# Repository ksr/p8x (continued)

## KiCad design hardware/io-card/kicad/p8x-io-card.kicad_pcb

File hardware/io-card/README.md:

# I/O Card

> **Theory of operation:** [p8x-io-card-theory.md](p8x-io-card-theory.md) — deep walkthrough of inputs/outputs, signal flow, and logic.

All memory-mapped I/O lives here: an 8-switch input port, an 8-LED output port,
**two** RS-232 serial channels via 6850 ACIAs (rev B), and a passive **bus-monitor**
LED display that turns the machine into an Altair-style "watch it think" front panel.

> **Rev B (2026-09-19)** — the routed KiCad board in [`kicad/`](kicad/README.md)
> (not yet fabricated) adds a second 6850 (**U17**, ACIA2 at `$FF08/09`, the
> Kermit / serial-terminal port) on the MAX232's second channel, with its E-gate
> inverter in **U18** (74HCT14). Each channel has its own **DB9** socket and a
> 2×3 jumper block that swaps RX/TX (straight or null-modem). A DS1302 real-time
> clock (**U16**) is provisioned but not fitted (DNP): it is a bit-banged 3-wire
> part on header J3, not memory-mapped. The text below describes the rev A
> circuit, which rev B keeps.

| Address | Port |
|---------|------|
| `$FF00` | Switch input — 8 toggle switches → data bus on read |
| `$FF02` | LED output — 74374 latch → 8 LEDs on write |
| `$FF04` | 6850 ACIA control/status |
| `$FF05` | 6850 ACIA data (RS-232 TX/RX) |
| `$FF08` | ACIA2 control/status (rev B) |
| `$FF09` | ACIA2 data (rev B) |

> This README describes the circuit as actually built in
> [`generators/gen_eagle.py`](../../generators/gen_eagle.py). See
> [p8x-system-design.md §7](../../docs/p8x-system-design.md) for the overview and
> [p8x-bus-definition.md](../backplane/p8x-bus-definition.md) for bus pins.

## Chip inventory

| Ref | Device | Role |
|-----|--------|------|
| U1 | 7430 | 8-input NAND — I/O page ($FFxx) detector |
| U2 | 74138 | Port decoder (A1–A3 → up to 8 port selects) |
| U3 | 74138 | DOE decoder (read enable) |
| U4 | 74138 | DLD decoder (write strobe) |
| U5 | 74HCT32 | OR glue (read/write strobe gating) |
| U6 | 74HCT08 | AND glue (ACIA enable) |
| U7 | 74161 | Baud-rate divider |
| U8 | MAX232 | RS-232 level shifter (the one non-TTL part) |
| U9 | 74244 | Switch-input buffer |
| U10 | 74374 | LED output latch |
| U11–U13 | 74244 | Bus monitors — A0–7, A8–15, D0–7 |
| U14 | 6850 | ACIA (asynchronous serial) |
| U15 | 74HCT00 | NAND glue |
| U16 | DS1302 | Real-time clock, DNP (rev B; 3-wire on J3, not memory-mapped) |
| U17 | 6850 | ACIA2 at `$FF08/09` (rev B) |
| U18 | 74HCT14 | Inverter — ACIA2 enable gate (rev B) |
| X2 | 2.4576 MHz osc | Baud clock source |

## How it works

### Port decoding
U1 (7430) detects the `$FFxx` page exactly as on the memory card. Within the page,
U2 (74138) decodes the low address lines into individual port selects (`-P0`, `-P1`,
`-P2`, …). Read vs write comes from the DOE decoder (U3 → `-RD`) and DLD decoder
(U4 → `-MEMW`), gated in U5/U6 into per-port read/write strobes.

### Switch input ($FF00)
Eight toggle switches with a SIP pull-up network feed a 74244 (U9). On a read of
`$FF00`, U9 is enabled and drives the switch states onto D0–D7.

### LED output ($FF02)
On a write to `$FF02`, the 74374 (U10) latches D0–D7. Its outputs drive an LED bank
through series-resistor networks, so the port value is visible at a glance.

### Serial (6850 ACIA, $FF04–$FF05)
The **6850 ACIA** (U14) handles asynchronous serial. Its enable is the `$FF04/05`
port select gated with the clock (U6/U15) for correct E-clock timing. A **74161**
(U7) divides the dedicated **2.4576 MHz** oscillator (X2) by 16 to make the
TX/RX baud clock. The **MAX232** (U8) — the one concession to non-TTL parts —
converts the ACIA's TTL levels to/from RS-232 ±voltages on the serial header,
using its four external charge-pump capacitors.

### Bus-monitor display (passive)
Three 74244 buffers (U11/U12/U13) permanently sample A0–7, A8–15, and D0–7 and
drive three LED banks. They cost nothing logically — no decode, no bus access —
but combined with the control card's single-step button they let you literally
watch the address and data buses change one microcycle at a time.

## Bus codes this card owns
- **DOE:** 7 = read (the active port drives D0–D7) — shared decode convention with memory
- **DLD:** 7 = write (`MEMW`) — the active port latches D0–D7

## LEDs
PWR (green), IOSEL (yellow — an I/O port is selected), plus the LED output port and
the 24-bit bus-monitor banks.

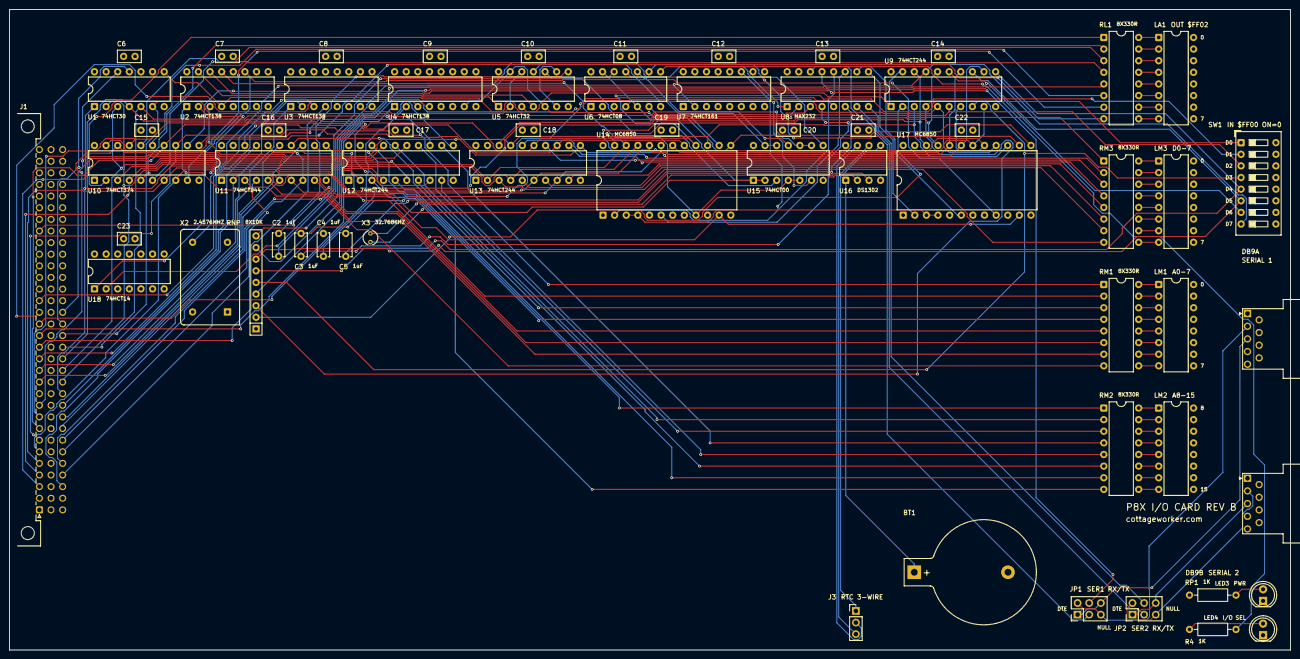
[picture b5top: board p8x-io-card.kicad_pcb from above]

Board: 4 copper layers, 280.0 x 140.0 mm, 63 parts (0 on the bottom side), 154 nets.

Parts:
BT1: CR2032; BatteryHolder_Keystone_103_1x20mm
C2, C3, C4, C5: 1uF; C_Disc_D5.0mm_W2.5mm_P5.00mm
C6, C7, C8, C9, C10, C11, C12, C13, C14, C15, C16, C17, C18, C19, C20, C21, C22, C23: 100nF; C_Disc_D5.0mm_W2.5mm_P2.50mm
DB9A: SERIAL1; DSUB-9_Socket_Horizontal_P2.77x2.54mm_EdgePinOffset9.40mm
DB9B: SERIAL2; DSUB-9_Socket_Horizontal_P2.77x2.54mm_EdgePinOffset9.40mm
J1: MABC96R; DIN41612_C_3x32_Male_Horizontal_THT
J3: 1x3; PinHeader_1x03_P2.54mm_Vertical
JP1: S1 SWAP; PinHeader_2x03_P2.54mm_Vertical
JP2: S2 SWAP; PinHeader_2x03_P2.54mm_Vertical
LA1: 8-LED BAR; DIP-16_W7.62mm
LED3: GRN; LED_D5.0mm
LED4: YEL; LED_D5.0mm
LM1: A0-7; DIP-16_W7.62mm
LM2: A8-15; DIP-16_W7.62mm
LM3: D0-7; DIP-16_W7.62mm
R4: 1K; R_Axial_DIN0207_L6.3mm_D2.5mm_P10.16mm_Horizontal
RL1: 8X330R; DIP-16_W7.62mm
RM1, RM2, RM3: 8X330R; DIP-16_W7.62mm
RNP: 8X10K; R_Array_SIP9
RP1: 1K; R_Axial_DIN0207_L6.3mm_D2.5mm_P10.16mm_Horizontal
SW1: INPUT; SW_DIP_SPSTx08_Slide_9.78x22.5mm_W7.62mm_P2.54mm
U1: 74HCT30; DIP-14_W7.62mm
U2, U3, U4: 74HCT138; DIP-16_W7.62mm
U5: 74HCT32; DIP-14_W7.62mm
U6: 74HCT08; DIP-14_W7.62mm
U7: 74HCT161; DIP-16_W7.62mm
U8: MAX232; DIP-16_W7.62mm
U9, U11, U12, U13: 74HCT244; DIP-20_W7.62mm
U10: 74HCT374; DIP-20_W7.62mm
U14, U17: 6850; DIP-24_W15.24mm
U15: 74HCT00; DIP-14_W7.62mm
U16: DS1302; DIP-8_W7.62mm
U18: 74HCT14; DIP-14_W7.62mm
X2: 2.4576MHZ; Oscillator_DIP-14
X3: 32.768KHZ; Crystal_Round_D3.0mm_Vertical

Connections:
-MEMW: U4.7, U5.5, U5.13, U14.13, U17.13
-P0: U2.15, U5.1
-P1: U2.14, U5.4
-P2: U2.13, U14.9, U15.4, U15.5
-P4: U2.11, U17.9, U18.1
-RD: U3.7, U5.2, U5.12
-SWOE: U5.3, U9.1, U9.19
A0: J1.c3, U11.2, U14.11, U17.11
A1: J1.c4, U2.1, U11.4
A2: J1.c5, U2.2, U11.6
A3: J1.c6, U2.3, U11.8
A4: J1.c7, U11.11
A5: J1.c8, U11.13
A6: J1.c9, U11.15
A7: J1.c10, U11.17
A8: J1.c11, U1.1, U12.2
A9: J1.c12, U1.2, U12.4
A10: J1.c13, U1.3, U12.6
A11: J1.c14, U1.4, U12.8
A12: J1.c15, U1.5, U12.11
A13: J1.c16, U1.6, U12.13
A14: J1.c17, U1.11, U12.15
A15: J1.c18, U1.12, U12.17
ACCP: U6.10, U15.11
BCLK: U7.11, U14.3, U14.4, U17.3, U17.4
BOEISH: U5.11, U15.12, U15.13
BOSC: U7.2, X2.8
C1MN: C2.2, U8.3
C1PN: C2.1, U8.1
C2MN: C3.2, U8.5
C2PN: C3.1, U8.4
CLKB: J1.a25, U6.5, U6.13, U15.1, U15.2
CLKBN: U5.10, U15.3
D0: J1.a3, U9.18, U10.3, U13.2, U14.22, U17.22
D1: J1.a4, U9.16, U10.4, U13.4, U14.21, U17.21
D2: J1.a5, U9.14, U10.7, U13.6, U14.20, U17.20
D3: J1.a6, U9.12, U10.8, U13.8, U14.19, U17.19
D4: J1.a7, U9.9, U10.13, U13.11, U14.18, U17.18
D5: J1.a8, U9.7, U10.14, U13.13, U14.17, U17.17
D6: J1.a9, U9.5, U10.17, U13.15, U14.16, U17.16
D7: J1.a10, U9.3, U10.18, U13.17, U14.15, U17.15
DLD0: J1.a16, U4.1
DLD1: J1.a17, U4.2
DLD2: J1.a18, U4.3
DLD3: J1.a19, U4.4
DOE0: J1.a12, U3.1
DOE1: J1.a13, U3.2
DOE2: J1.a14, U3.3
DOE3: J1.a15, U3.4
E2: U6.11, U17.14
EEN: U6.6, U14.14
GND: BT1.2, C4.2, C5.2, C6.2, C7.2, C8.2, C9.2, C10.2, C11.2, C12.2, C13.2, C14.2, C15.2, C16.2, C17.2, C18.2, C19.2, C20.2, C21.2, C22.2, C23.2, DB9A.5, DB9B.5, J1.a31, J1.a32, J1.b3, J1.b5, J1.b7, J1.b9, J1.b11, J1.b13, J1.b15, J1.b17, J1.b19, J1.b21, J1.b23, J1.b25, J1.b31, J1.b32, J1.c31, J1.c32, LA1.9, LA1.10, LA1.11, LA1.12, LA1.13, LA1.14, LA1.15, LA1.16, LED3.1, LED4.1, LM1.9, LM1.10, LM1.11, LM1.12, LM1.13, LM1.14, LM1.15, LM1.16, LM2.9, LM2.10, LM2.11, LM2.12, LM2.13, LM2.14, LM2.15, LM2.16, LM3.9, LM3.10, LM3.11, LM3.12, LM3.13, LM3.14, LM3.15, LM3.16, SW1.9, SW1.10, SW1.11, SW1.12, SW1.13, SW1.14, SW1.15, SW1.16, U1.7, U2.5, U2.8, U3.5, U3.8, U4.5, U4.8, U5.7, U6.1, U6.2, U6.7, U7.3, U7.4, U7.5, U7.6, U7.8, U8.15, U9.10, U10.1, U10.10, U11.1, U11.10, U11.19, U12.1, U12.10, U12.19, U13.1, U13.10, U13.19, U14.1, U14.23, U14.24, U15.7, U16.4, U17.1, U17.23, U17.24, U18.3, U18.5, U18.7, U18.9, U18.11, U18.13, X2.7
IOPG: U1.8, U2.4, U15.9, U15.10
IOPGN: U6.9, U15.8
LCK: U5.8, U10.11
LED4A: LED4.2, R4.1
LEDP: LED3.2, RP1.2
LP0: RL1.1, U10.2
LP1: RL1.2, U10.5
LP2: RL1.3, U10.6
LP3: RL1.4, U10.9
LP4: RL1.5, U10.12
LP5: RL1.6, U10.15
LP6: RL1.7, U10.16
LP7: RL1.8, U10.19
LR0: LA1.1, RL1.16
LR1: LA1.2, RL1.15
LR2: LA1.3, RL1.14
LR3: LA1.4, RL1.13
LR4: LA1.5, RL1.12
LR5: LA1.6, RL1.11
LR6: LA1.7, RL1.10
LR7: LA1.8, RL1.9
LW1: U5.6, U5.9
MA0: RM1.1, U11.18
MA1: RM1.2, U11.16
MA2: RM1.3, U11.14
MA3: RM1.4, U11.12
MA4: RM1.5, U11.9
MA5: RM1.6, U11.7
MA6: RM1.7, U11.5
MA7: RM1.8, U11.3
MA8: RM2.1, U12.18
MA9: RM2.2, U12.16
MA10: RM2.3, U12.14
MA11: RM2.4, U12.12
MA12: RM2.5, U12.9
MA13: RM2.6, U12.7
MA14: RM2.7, U12.5
MA15: RM2.8, U12.3
MD0: RM3.1, U13.18
MD1: RM3.2, U13.16
MD2: RM3.3, U13.14
MD3: RM3.4, U13.12
MD4: RM3.5, U13.9
MD5: RM3.6, U13.7
MD6: RM3.7, U13.5
MD7: RM3.8, U13.3
ML0_0: LM1.1, RM1.16
ML0_1: LM1.2, RM1.15
ML0_2: LM1.3, RM1.14
ML0_3: LM1.4, RM1.13
ML0_4: LM1.5, RM1.12
ML0_5: LM1.6, RM1.11
ML0_6: LM1.7, RM1.10
ML0_7: LM1.8, RM1.9
ML1_0: LM2.1, RM2.16
ML1_1: LM2.2, RM2.15
ML1_2: LM2.3, RM2.14
ML1_3: LM2.4, RM2.13
ML1_4: LM2.5, RM2.12
ML1_5: LM2.6, RM2.11
ML1_6: LM2.7, RM2.10
ML1_7: LM2.8, RM2.9
ML2_0: LM3.1, RM3.16
ML2_1: LM3.2, RM3.15
ML2_2: LM3.3, RM3.14
ML2_3: LM3.4, RM3.13
ML2_4: LM3.5, RM3.12
ML2_5: LM3.6, RM3.11
ML2_6: LM3.7, RM3.10
ML2_7: LM3.8, RM3.9
P2P: U6.4, U15.6
P4P: U6.12, U18.2
RTCCE: J3.1, U16.5
RTCIO: J3.3, U16.6
RTCSCLK: J3.2, U16.7
RTCX1: U16.2, X3.1
RTCX2: U16.3, X3.2
RXD: U8.12, U14.2
RXD2: U8.9, U17.2
S1RXD: DB9A.2, JP1.2, JP1.5
S1TXD: DB9A.3, JP1.1, JP1.6
S2RXD: DB9B.2, JP2.2, JP2.5
S2TXD: DB9B.3, JP2.1, JP2.6
SELP: R4.2, U6.8
SIN: JP1.4, U8.13
SIN2: JP2.4, U8.8
SOUT: JP1.3, U8.14
SOUT2: JP2.3, U8.7
SWN0: RNP.2, SW1.1, U9.2
SWN1: RNP.3, SW1.2, U9.4
SWN2: RNP.4, SW1.3, U9.6
SWN3: RNP.5, SW1.4, U9.8
SWN4: RNP.6, SW1.5, U9.11
SWN5: RNP.7, SW1.6, U9.13
SWN6: RNP.8, SW1.7, U9.15
SWN7: RNP.9, SW1.8, U9.17
TXD: U8.11, U14.6
TXD2: U8.10, U17.6
VBAT: BT1.1, U16.1
VCC: C6.1, C7.1, C8.1, C9.1, C10.1, C11.1, C12.1, C13.1, C14.1, C15.1, C16.1, C17.1, C18.1, C19.1, C20.1, C21.1, C22.1, C23.1, J1.a1, J1.a2, J1.b1, J1.b2, J1.c1, J1.c2, RNP.1, RP1.1, U1.14, U2.6, U2.16, U3.6, U3.16, U4.6, U4.16, U5.14, U6.14, U7.1, U7.7, U7.9, U7.10, U7.16, U8.16, U9.20, U10.20, U11.20, U12.20, U13.20, U14.8, U14.10, U14.12, U15.14, U16.8, U17.8, U17.10, U17.12, U18.14, X2.14
VMN: C5.1, U8.6
VPN: C4.1, U8.2

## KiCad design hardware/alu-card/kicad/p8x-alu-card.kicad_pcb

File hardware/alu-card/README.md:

# ALU Card

> **Theory of operation:** [p8x-alu-card-theory.md](p8x-alu-card-theory.md) — deep walkthrough of inputs/outputs, signal flow, and logic.

Holds the two ALU operand registers (**A**, **B**), the two hidden microcode
temporaries (**T**, **T2**), the **74181-based ALU** with a post-ALU shifter, and
the **FLAGS** register. All arithmetic and logic happens here.

> This README describes the circuit as actually built in
> [`generators/gen_eagle.py`](../../generators/gen_eagle.py). See
> [p8x-system-design.md §5](../../docs/p8x-system-design.md) for the overview and
> [p8x-bus-definition.md](../backplane/p8x-bus-definition.md) for bus pins.

## Chip inventory

| Ref | Device | Role |
|-----|--------|------|
| U1, U2 | 74377 + 74244 | A register (load latch + bus-drive buffer) |
| U3, U4 | 74377 + 74244 | B register |
| U5, U6 | 74377 + 74244 | T register (hidden temp) |
| U7, U8 | 74377 + 74244 | T2 register (hidden temp) |
| U9, U10 | 74181 | ALU, low and high nibble |
| U11 | 74182 | Carry-lookahead generator across the two 74181s |
| U12–U15 | 74157 | Two-stage shifter (pass / <<1 / >>1) |
| U16 | 74244 | ALU-result bus driver |
| U17 | 74175 | FLAGS register (C, Z, N, V) |
| U18 | 74260 | Zero-detect NOR over the result |
| U19 | 74HCT08 | AND glue (zero combine, flag-clock gate) |
| U20 | 74138 | DOE decoder (codes 1–6) |
| U21 | 74138 | DLD decoder (codes 1–5) |
| U22 | 74157 | Flag mux — select computed flags vs restore-from-bus |
| U23 | 74244 | FLAGS → data bus driver |
| U24, U25 | 74HCT32 / 74HCT00 | Flag-load and restore gating |

## How it works

### The four registers
A, B, T, T2 are each a **74377** (8-bit latch with a load enable) paired with a
**74244** output buffer. The 74377 loads from the data bus when its DLD code is
decoded by U21 (`-LDA`/`-LDB`/`-LDT`/`-LDT2`). The 74244 drives the register's value
back onto the data bus when its DOE code is decoded by U20. A and B also feed the
74181 inputs directly and continuously — they don't need to be on the bus for the
ALU to operate on them.

### The ALU (74181 + 74182)
Two 74181s (U9 low nibble, U10 high nibble) form the 8-bit ALU. Function is set by
the backplane lines **ALUS0–3** (operation select), **ALUM** (logic vs arithmetic),
and **CIN** (carry in). Instead of rippling carry between the two 74181s, the
**74182** carry-lookahead generator (U11) takes their propagate/generate outputs
(`!P`/`!G`) and produces the fast intermediate carry `CNX` into the high nibble —
keeping the carry chain short and fast.

> **Carry flag polarity quirk:** the C flag latches the *raw* 74181 `Cn+4` pin,
> which is **active-low** (C=1 means *no* carry out). This is deliberate and the
> emulator reproduces it faithfully — do not "fix" it. See
> [p8x-bus-definition.md §3.8](../backplane/p8x-bus-definition.md).

### The shifter
Two stages of 74157 muxes (U12/U13 then U14/U15) sit after the ALU, selected by
**SH0/SH1**, giving pass-through, shift-left, or shift-right. The shift-in bit is
wired to CIN. The shifted result is driven onto the data bus by U16 (74244) when
DOE selects the ALU result (code 5).

### Flags
- **Z** (zero): U18 (74260) NORs the result bits, combined in U19 — asserted when
  the whole 8-bit result is zero.
- **N** (negative): bit 7 of the result.
- **C** (carry): the raw 74181 `Cn+4` (see quirk above).
- **V** (overflow): **hardwired 0 in rev A** — unimplemented (see BACKLOG).

The 74175 (U17) latches all four flags, but **only when LDF is asserted** (the flag
clock is gated by U19/U24 so non-ALU cycles don't disturb the flags). The U22 74157
mux lets FLAGS be either freshly computed *or* restored from the data bus (DLD
code 5, for PLP-style flag pops), and U23 (74244) drives FLAGS onto the bus for
PHP-style pushes (DOE code 6).

## Bus codes this card owns
- **DOE:** 1=A, 2=B, 3=T, 4=T2, 5=ALU result, 6=FLAGS
- **DLD:** 1=A, 2=B, 3=T, 4=T2, 5=FLAGS (restore)

## LEDs
PWR (green), ALU (green — result on bus), LDF (yellow — flags latching).

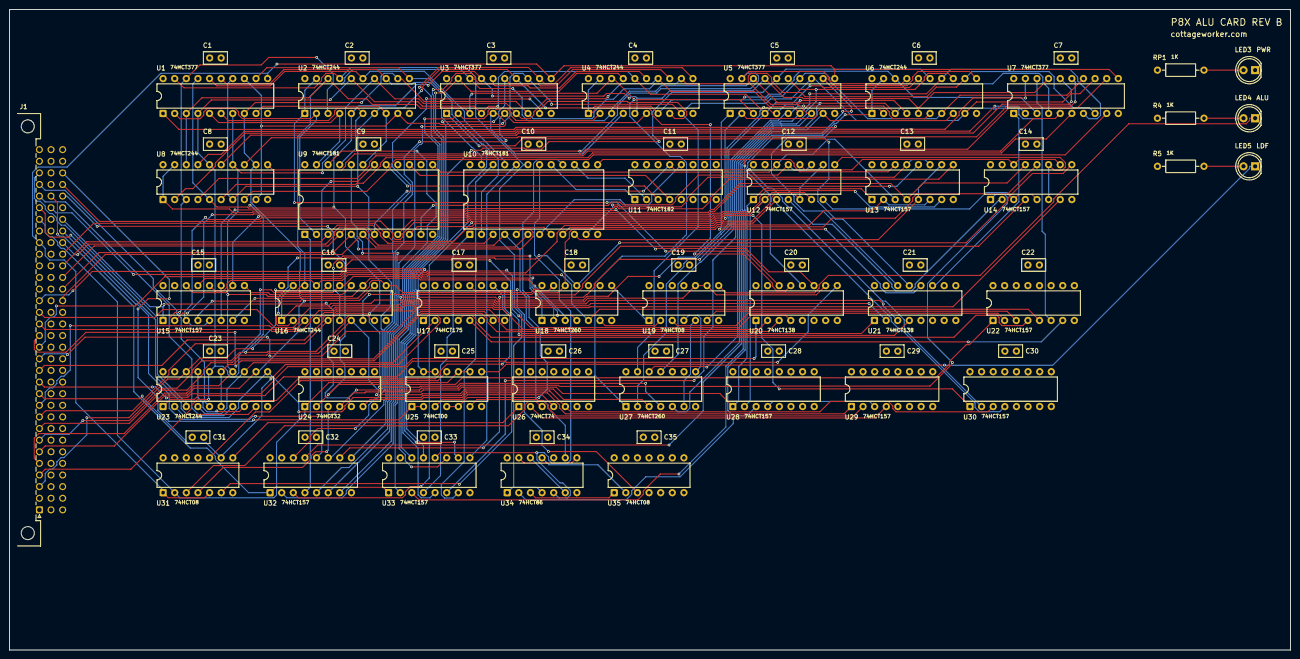
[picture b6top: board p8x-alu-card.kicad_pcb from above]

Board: 4 copper layers, 280.0 x 140.0 mm, 77 parts (0 on the bottom side), 151 nets.

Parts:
C1, C2, C3, C4, C5, C6, C7, C8, C9, C10, C11, C12, C13, C14, C15, C16, C17, C18, C19, C20, C21, C22, C23, C24, C25, C26, C27, C28, C29, C30, C31, C32, C33, C34, C35: 100nF; C_Disc_D5.0mm_W2.5mm_P2.50mm
J1: MABC96R; DIN41612_C_3x32_Male_Horizontal_THT
LED3, LED4: GRN; LED_D5.0mm
LED5: YEL; LED_D5.0mm
R4, R5: 1K; R_Axial_DIN0207_L6.3mm_D2.5mm_P10.16mm_Horizontal
RP1: 1K; R_Axial_DIN0207_L6.3mm_D2.5mm_P10.16mm_Horizontal
U1, U3, U5, U7: 74HCT377; DIP-20_W7.62mm
U2, U4, U6, U8, U16, U23: 74HCT244; DIP-20_W7.62mm
U9, U10: 74HCT181; DIP-24_W15.24mm
U11: 74HCT182; DIP-16_W7.62mm
U12, U13, U14, U15, U22, U28, U29, U30, U32, U33: 74HCT157; DIP-16_W7.62mm
U17: FLAGS; DIP-16_W7.62mm
U18, U27: 74HCT260; DIP-14_W7.62mm
U19, U31, U35: 74HCT08; DIP-14_W7.62mm
U20, U21: 74HCT138; DIP-16_W7.62mm
U24: 74HCT32; DIP-14_W7.62mm
U25: 74HCT00; DIP-14_W7.62mm
U26: 74HCT74; DIP-14_W7.62mm
U34: 74HCT86; DIP-14_W7.62mm

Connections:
-CCLR: U26.1, U31.8
-CLRCb: U25.11, U31.10
-DOEA: U2.1, U2.19, U20.14
-DOEALU: U16.1, U16.19, U19.9, U19.10, U20.10
-DOEB: U4.1, U4.19, U20.13
-DOEFLG: U20.9, U23.1
-DOET: U6.1, U6.19, U20.12
-DOET2: U8.1, U8.19, U20.11
-LDA: U1.1, U21.14
-LDB: U3.1, U21.13
-LDT: U5.1, U21.12
-LDT2: U7.1, U21.11
-RES: J1.a11, U17.1, U31.9
-SETCb: U25.3, U26.4
ALUK: LED4.1, U19.8
ALUM: J1.c23, U9.8, U10.8
ALUS0: J1.c19, U9.6, U10.6
ALUS1: J1.c20, U9.5, U10.5
ALUS2: J1.c21, U9.4, U10.4, U34.9
ALUS3: J1.c22, U9.3, U10.3
AQ0: U1.2, U2.2, U9.2
AQ1: U1.5, U2.4, U9.23
AQ2: U1.6, U2.6, U9.21
AQ3: U1.9, U2.8, U9.19
AQ4: U1.12, U2.11, U10.2
AQ5: U1.15, U2.13, U10.23
AQ6: U1.16, U2.15, U10.21
AQ7: U1.19, U2.17, U10.19, U34.1, U34.4
BMX0: U9.1, U32.4
BMX1: U9.22, U32.7
BMX2: U9.20, U32.9
BMX3: U9.18, U32.12
BMX4: U10.1, U33.4
BMX5: U10.22, U33.7
BMX6: U10.20, U33.9
BMX7: U10.18, U33.12, U34.5
BQ0: U3.2, U4.2, U32.2
BQ1: U3.5, U4.4, U32.5
BQ2: U3.6, U4.6, U32.11
BQ3: U3.9, U4.8, U32.14
BQ4: U3.12, U4.11, U33.2
BQ5: U3.15, U4.13, U33.5
BQ6: U3.16, U4.15, U33.11
BQ7: U3.19, U4.17, U33.14
BSEL: J1.b28, U32.1, U33.1
CFLG: U10.16, U25.4, U25.5
CFLGI: U25.6, U29.2
CG0: U9.17, U11.3
CG1: U10.17, U11.1
CIN: J1.c24, U9.7, U11.13, U30.2
CLK: J1.a24, U1.11, U3.11, U5.11, U7.11, U31.1, U31.5
CLKFC: U26.3, U31.3
CLKFZN: U17.9, U31.6
CLRC: J1.b27, U25.12, U25.13
CNX: U10.7, U11.12
CP0: U9.15, U11.4
CP1: U10.15, U11.2
D0: J1.a3, U1.3, U2.18, U3.3, U4.18, U5.3, U6.18, U7.3, U8.18, U16.18, U23.18, U27.1
D1: J1.a4, U1.4, U2.16, U3.4, U4.16, U5.4, U6.16, U7.4, U8.16, U16.16, U23.16, U27.2
D2: J1.a5, U1.7, U2.14, U3.7, U4.14, U5.7, U6.14, U7.7, U8.14, U16.14, U23.14, U27.11
D3: J1.a6, U1.8, U2.12, U3.8, U4.12, U5.8, U6.12, U7.8, U8.12, U16.12, U23.12, U27.12
D4: J1.a7, U1.13, U2.9, U3.13, U4.9, U5.13, U6.9, U7.13, U8.9, U16.9, U27.13
D5: J1.a8, U1.14, U2.7, U3.14, U4.7, U5.14, U6.7, U7.14, U8.7, U16.7, U27.3
D6: J1.a9, U1.17, U2.5, U3.17, U4.5, U5.17, U6.5, U7.17, U8.5, U16.5, U27.4
D7: J1.a10, U1.18, U2.3, U3.18, U4.3, U5.18, U6.3, U7.18, U8.3, U16.3, U22.6, U27.5
DLD0: J1.a16, U21.1
DLD1: J1.a17, U21.2
DLD2: J1.a18, U21.3
DLD3: J1.a19, U21.4
DOE0: J1.a12, U20.1
DOE1: J1.a13, U20.2
DOE2: J1.a14, U20.3
DOE3: J1.a15, U20.4
F0: U9.9, U12.2, U12.6, U28.2
F1: U9.10, U12.5, U12.10
F2: U9.11, U12.11, U12.13
F3: U9.13, U12.14, U13.3
F4: U10.9, U13.2, U13.6
F5: U10.10, U13.5, U13.10
F6: U10.11, U13.11, U13.13
F7: U10.13, U13.14, U28.3, U34.2
FC: J1.a27, U23.9
FENZN: U24.3, U31.4
FN: J1.a29, U23.5
FQC: U23.2, U23.11, U26.5, U30.3
FQN: U17.7, U23.6, U23.15
FQV: U17.10, U23.8, U23.17
FQZ: U17.2, U23.4, U23.13
FV: J1.a30, U23.3
FZ: J1.a28, U23.7
G0: U12.4, U14.2
G1: U12.7, U14.3, U14.5
G2: U12.9, U14.6, U14.11
G3: U12.12, U14.10, U14.14
G4: U13.4, U14.13, U15.2
G5: U13.7, U15.3, U15.5
G6: U13.9, U15.6, U15.11
G7: U13.12, U15.10, U15.14
GND: C1.2, C2.2, C3.2, C4.2, C5.2, C6.2, C7.2, C8.2, C9.2, C10.2, C11.2, C12.2, C13.2, C14.2, C15.2, C16.2, C17.2, C18.2, C19.2, C20.2, C21.2, C22.2, C23.2, C24.2, C25.2, C26.2, C27.2, C28.2, C29.2, C30.2, C31.2, C32.2, C33.2, C34.2, C35.2, J1.a31, J1.a32, J1.b3, J1.b5, J1.b7, J1.b9, J1.b11, J1.b13, J1.b15, J1.b17, J1.b19, J1.b21, J1.b23, J1.b25, J1.b31, J1.b32, J1.c31, J1.c32, LED3.1, U1.10, U2.10, U3.10, U4.10, U5.10, U6.10, U7.10, U8.10, U9.12, U10.12, U11.8, U12.8, U12.15, U13.8, U13.15, U14.8, U14.15, U15.8, U15.15, U16.10, U17.8, U18.7, U18.9, U18.10, U19.7, U19.12, U19.13, U20.5, U20.8, U21.5, U21.8, U22.8, U22.15, U23.10, U23.19, U24.7, U24.9, U24.10, U24.12, U24.13, U25.7, U26.7, U26.11, U26.12, U27.7, U27.9, U27.10, U28.8, U28.15, U29.8, U29.15, U30.8, U30.15, U31.7, U31.12, U31.13, U32.8, U32.15, U33.8, U33.15, U34.7, U35.4, U35.5, U35.7, U35.9, U35.10, U35.12, U35.13
LDF: J1.a26, U24.1, U25.9, U25.10, U31.2
LDFK: LED5.1, U25.8
LDZN: J1.c28, U22.1, U24.2
LEDAL: LED4.2, R4.2
LEDLF: LED5.2, R5.2
LEDP: LED3.2, RP1.2
NC: U26.2, U29.4
NS2: U34.8, U34.13
NSRC: U17.5, U22.7
R0: U14.4, U16.2, U18.1
R1: U14.7, U16.4, U18.2
R2: U14.9, U16.6, U18.11
R3: U14.12, U16.8, U18.12
R4: U15.4, U16.11, U18.13
R5: U15.7, U16.13, U18.3
R6: U15.9, U16.15, U18.4
R7: U15.12, U16.17, U18.5, U22.5
SETC: J1.c30, U25.1, U25.2
SH0: J1.c25, U12.1, U13.1, U24.4, U28.1
SH1: J1.c26, U14.1, U15.1, U24.5
SHANY: U24.6, U29.1
SHCIN: J1.c29, U30.1
SHIN: U12.3, U15.13, U30.4
SHOUT: U28.4, U29.3
T2Q0: U7.2, U8.2
T2Q1: U7.5, U8.4
T2Q2: U7.6, U8.6
T2Q3: U7.9, U8.8
T2Q4: U7.12, U8.11
T2Q5: U7.15, U8.13
T2Q6: U7.16, U8.15
T2Q7: U7.19, U8.17
TQ0: U5.2, U6.2, U32.3
TQ1: U5.5, U6.4, U32.6
TQ2: U5.6, U6.6, U32.10
TQ3: U5.9, U6.8, U32.13
TQ4: U5.12, U6.11, U33.3
TQ5: U5.15, U6.13, U33.6
TQ6: U5.16, U6.15, U33.10
TQ7: U5.19, U6.17, U33.13
VCC: C1.1, C2.1, C3.1, C4.1, C5.1, C6.1, C7.1, C8.1, C9.1, C10.1, C11.1, C12.1, C13.1, C14.1, C15.1, C16.1, C17.1, C18.1, C19.1, C20.1, C21.1, C22.1, C23.1, C24.1, C25.1, C26.1, C27.1, C28.1, C29.1, C30.1, C31.1, C32.1, C33.1, C34.1, C35.1, J1.a1, J1.a2, J1.b1, J1.b2, J1.c1, J1.c2, R4.1, R5.1, RP1.1, U1.20, U2.20, U3.20, U4.20, U5.20, U6.20, U7.20, U8.20, U9.24, U10.24, U11.5, U11.6, U11.14, U11.15, U11.16, U12.16, U13.16, U14.16, U15.16, U16.20, U17.16, U18.14, U19.14, U20.6, U20.16, U21.6, U21.16, U22.16, U23.20, U24.14, U25.14, U26.10, U26.13, U26.14, U27.14, U28.16, U29.16, U30.16, U31.14, U32.16, U33.16, U34.10, U34.14, U35.14
VSRC: U17.12, U35.3
VX1: U34.3, U35.1
VX2: U34.6, U34.12
VX4: U34.11, U35.2
ZBH: U19.5, U27.6
ZBL: U19.4, U27.8
ZBUS: U19.6, U22.3
ZFLG: U19.3, U22.2
ZH: U18.6, U19.2
ZL: U18.8, U19.1
ZSRC: U17.4, U22.4

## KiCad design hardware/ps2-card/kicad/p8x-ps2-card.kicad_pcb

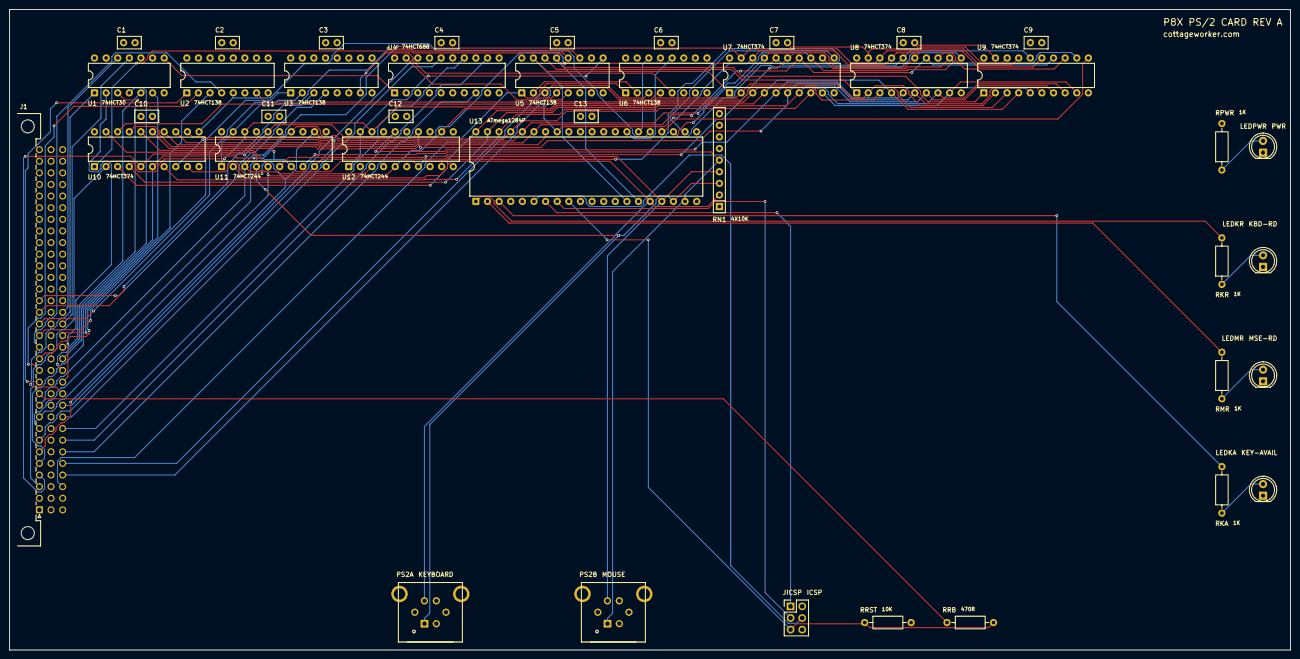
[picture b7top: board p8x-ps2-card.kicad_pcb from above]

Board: 4 copper layers, 280.0 x 140.0 mm, 41 parts (0 on the bottom side), 74 nets.

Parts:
C1, C2, C3, C4, C5, C6, C7, C8, C9, C10, C11, C12, C13: 100nF; C_Disc_D5.0mm_W2.5mm_P2.50mm
J1: MABC96R; DIN41612_C_3x32_Male_Horizontal_THT
JICSP: ICSP; PinHeader_2x03_P2.54mm_Vertical
LEDKA: GRN; LED_D5.0mm
LEDKR: YEL; LED_D5.0mm
LEDMR: YEL; LED_D5.0mm
LEDPWR: GRN; LED_D5.0mm
PS2A: PS2-KBD; MiniDIN6_RA_PS2
PS2B: PS2-MOUSE; MiniDIN6_RA_PS2
RKA: 1K; R_Axial_DIN0207_L6.3mm_D2.5mm_P10.16mm_Horizontal
RKR: 1K; R_Axial_DIN0207_L6.3mm_D2.5mm_P10.16mm_Horizontal
RMR: 1K; R_Axial_DIN0207_L6.3mm_D2.5mm_P10.16mm_Horizontal
RN1: 4X10K; R_Array_SIP9
RPWR: 1K; R_Axial_DIN0207_L6.3mm_D2.5mm_P10.16mm_Horizontal
RRB: 470R; R_Axial_DIN0207_L6.3mm_D2.5mm_P10.16mm_Horizontal
RRST: 10K; R_Axial_DIN0207_L6.3mm_D2.5mm_P10.16mm_Horizontal
U1: 74HCT30; DIP-14_W7.62mm
U2, U3, U5, U6: 74HCT138; DIP-16_W7.62mm
U4: WIN CMP; DIP-20_W7.62mm
U7, U8, U9, U10: 74HCT374; DIP-20_W7.62mm
U11, U12: 74HCT244; DIP-20_W7.62mm
U13: PS/2 MCU; DIP-40_W15.24mm

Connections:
-MEMW: U3.7, U6.5
-PSSEL: U4.19, U5.4, U6.4
-RD: U2.7, U5.5
-RES: J1.a11, RRB.1
-RESET: JICSP.5, RRB.2, RRST.1, U13.9
-RR0: U5.15, U7.1, U13.14
-RR1: U5.14, U8.1
-RR2: U5.13, U9.1, U13.15
-RR3: U5.12, U10.1
-RR4: U5.11, U11.1, U11.19
-RR6: U5.9, U12.1, U12.19
-WR1: U6.14, U13.26
-WR3: U6.12, U13.27
A0: J1.c3, U5.1, U6.1
A1: J1.c4, U5.2, U6.2
A2: J1.c5, U5.3, U6.3
A3: J1.c6, U4.8
A4: J1.c7, U4.12
A5: J1.c8, U4.14
A6: J1.c9, U4.16
A7: J1.c10, U4.18
A8: J1.c11, U1.1
A9: J1.c12, U1.2
A10: J1.c13, U1.3
A11: J1.c14, U1.4
A12: J1.c15, U1.5
A13: J1.c16, U1.6
A14: J1.c17, U1.11
A15: J1.c18, U1.12
D0: J1.a3, U7.2, U8.2, U9.2, U10.2, U11.18, U12.18
D1: J1.a4, U7.5, U8.5, U9.5, U10.5, U11.16, U12.16
D2: J1.a5, U7.6, U8.6, U9.6, U10.6, U11.14, U12.14
D3: J1.a6, U7.9, U8.9, U9.9, U10.9, U11.12, U12.12
D4: J1.a7, U7.12, U8.12, U9.12, U10.12, U11.9, U12.9
D5: J1.a8, U7.15, U8.15, U9.15, U10.15, U11.7, U12.7
D6: J1.a9, U7.16, U8.16, U9.16, U10.16, U11.5, U12.5
D7: J1.a10, U7.19, U8.19, U9.19, U10.19, U11.3, U12.3
DLD0: J1.a16, U3.1
DLD1: J1.a17, U3.2
DLD2: J1.a18, U3.3
DLD3: J1.a19, U3.4
DOE0: J1.a12, U2.1
DOE1: J1.a13, U2.2
DOE2: J1.a14, U2.3
DOE3: J1.a15, U2.4
GND: C1.2, C2.2, C3.2, C4.2, C5.2, C6.2, C7.2, C8.2, C9.2, C10.2, C11.2, C12.2, C13.2, J1.a31, J1.a32, J1.b3, J1.b5, J1.b7, J1.b9, J1.b11, J1.b13, J1.b15, J1.b17, J1.b19, J1.b21, J1.b23, J1.b25, J1.b31, J1.b32, J1.c31, J1.c32, JICSP.6, LEDKA.1, LEDKR.1, LEDMR.1, LEDPWR.1, PS2A.3, PS2A.SH, PS2B.3, PS2B.SH, U1.7, U2.5, U2.8, U3.5, U3.8, U4.2, U4.3, U4.4, U4.5, U4.6, U4.7, U4.10, U4.13, U4.17, U5.8, U6.8, U7.10, U8.10, U9.10, U10.10, U11.10, U11.11, U11.13, U11.15, U11.17, U12.6, U12.10, U12.11, U12.13, U12.17, U13.11, U13.31
IOPG: U1.8, U4.1
LDA: U7.11, U13.22
LDB: U9.11, U13.24
LDSA: U8.11, U13.23
LDSB: U10.11, U13.25
LKA: RKA.2, U13.3
LKAA: LEDKA.2, RKA.1
LKR: RKR.2, U13.1
LKRA: LEDKR.2, RKR.1
LMR: RMR.2, U13.2
LMRA: LEDMR.2, RMR.1
LPWRA: LEDPWR.2, RPWR.1
MB0: U7.3, U8.3, U9.3, U10.3, U13.40
MB1: U7.4, U8.4, U9.4, U10.4, U13.39
MB2: U7.7, U8.7, U9.7, U10.7, U13.38
MB3: U7.8, U8.8, U9.8, U10.8, U13.37
MB4: U7.13, U8.13, U9.13, U10.13, U13.36
MB5: U7.14, U8.14, U9.14, U10.14, U13.35
MB6: U7.17, U8.17, U9.17, U10.17, U13.34
MB7: U7.18, U8.18, U9.18, U10.18, U13.33
MISO: JICSP.1, U13.7
MOSI: JICSP.4, U13.6
PS2CKA: PS2A.5, RN1.2, U11.2, U13.16
PS2CKB: PS2B.5, RN1.4, U11.6, U13.17
PS2DA: PS2A.1, RN1.3, U11.4, U13.18
PS2DB: PS2B.1, RN1.5, U11.8, U13.19
SCK: JICSP.3, U13.8
VCC: C1.1, C2.1, C3.1, C4.1, C5.1, C6.1, C7.1, C8.1, C9.1, C10.1, C11.1, C12.1, C13.1, J1.a1, J1.a2, J1.b1, J1.b2, J1.c1, J1.c2, JICSP.2, PS2A.4, PS2B.4, RN1.1, RPWR.2, RRST.2, U1.14, U2.6, U2.16, U3.6, U3.16, U4.9, U4.11, U4.15, U4.20, U5.6, U5.16, U6.6, U6.16, U7.20, U8.20, U9.20, U10.20, U11.20, U12.2, U12.4, U12.8, U12.15, U12.20, U13.10, U13.30

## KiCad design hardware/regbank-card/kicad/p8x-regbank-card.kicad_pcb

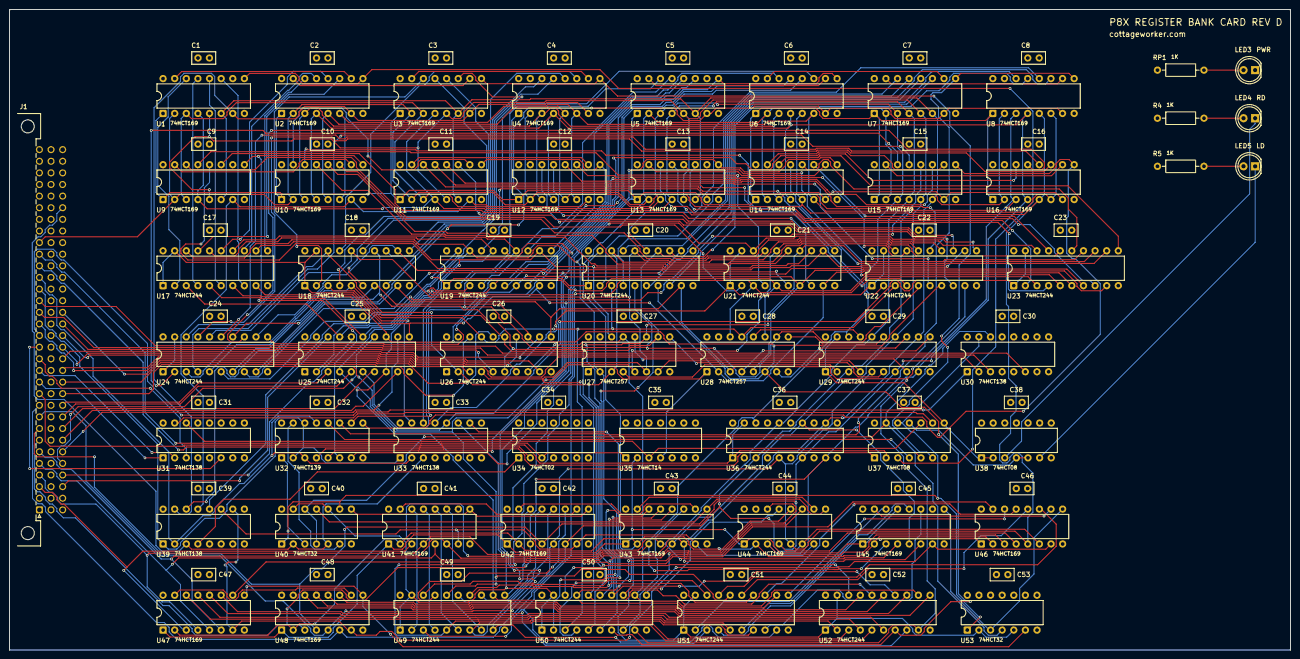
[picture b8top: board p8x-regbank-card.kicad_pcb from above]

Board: 4 copper layers, 280.0 x 140.0 mm, 113 parts (0 on the bottom side), 221 nets.

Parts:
C1, C2, C3, C4, C5, C6, C7, C8, C9, C10, C11, C12, C13, C14, C15, C16, C17, C18, C19, C20, C21, C22, C23, C24, C25, C26, C27, C28, C29, C30, C31, C32, C33, C34, C35, C36, C37, C38, C39, C40, C41, C42, C43, C44, C45, C46, C47, C48, C49, C50, C51, C52, C53: 100nF; C_Disc_D5.0mm_W2.5mm_P2.50mm
J1: MABC96R; DIN41612_C_3x32_Male_Horizontal_THT
LED3, LED4: GRN; LED_D5.0mm
LED5: YEL; LED_D5.0mm
R4, R5: 1K; R_Axial_DIN0207_L6.3mm_D2.5mm_P10.16mm_Horizontal
RP1: 1K; R_Axial_DIN0207_L6.3mm_D2.5mm_P10.16mm_Horizontal
U1, U2, U3, U4, U5, U6, U7, U8, U9, U10, U11, U12, U13, U14, U15, U16, U41, U42, U43, U44, U45, U46, U47, U48: 74HCT169; DIP-16_W7.62mm
U17, U18, U19, U20, U21, U22, U23, U24, U25, U26, U29, U36, U49, U50, U51, U52: 74HCT244; DIP-20_W7.62mm
U27, U28: 74HCT257; DIP-16_W7.62mm
U30, U31, U33, U39: 74HCT138; DIP-16_W7.62mm
U32: 74HCT139; DIP-16_W7.62mm
U34: 74HCT02; DIP-14_W7.62mm
U35: 74HCT14; DIP-14_W7.62mm
U37, U38: 74HCT08; DIP-14_W7.62mm
U40, U53: 74HCT32; DIP-14_W7.62mm

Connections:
-CNT0: U1.7, U2.7, U3.7, U4.7, U39.15
-CNT1: U5.7, U6.7, U7.7, U8.7, U39.14
-CNT2: U9.7, U10.7, U11.7, U12.7, U39.13
-CNT3: U13.7, U14.7, U15.7, U16.7, U39.12
-CNT4: U39.11, U41.7, U42.7, U43.7, U44.7
-CNT5: U39.10, U45.7, U46.7, U47.7, U48.7
-LDH: U30.14, U37.13, U40.4, U40.12, U53.4
-LDH0: U32.12, U37.4
-LDH0E: U3.9, U4.9, U37.6
-LDH1: U7.9, U8.9, U32.11
-LDH2: U11.9, U12.9, U32.10
-LDH3: U15.9, U16.9, U32.9
-LDH4: U40.11, U43.9, U44.9
-LDH5: U47.9, U48.9, U53.6
-LDHG: U32.15, U40.6
-LDL: U30.15, U37.12, U40.1, U40.9, U53.1
-LDL0: U32.4, U37.1
-LDL0E: U1.9, U2.9, U37.3
-LDL1: U5.9, U6.9, U32.5
-LDL2: U9.9, U10.9, U32.6
-LDL3: U13.9, U14.9, U32.7
-LDL4: U40.8, U41.9, U42.9
-LDL5: U45.9, U46.9, U53.3
-LDLG: U32.1, U40.3
-LDP: U37.11, U38.4, U38.5
-POE: U29.1, U29.19, U37.8, U38.1, U38.2
-POEH: U31.14, U35.3, U37.10
-POEL: U31.15, U37.9
-RES: J1.a11, U36.1, U36.19, U37.2, U37.5
-SEL0: U17.1, U17.19, U18.1, U18.19, U33.15
-SEL1: U19.1, U19.19, U20.1, U20.19, U33.14
-SEL2: U21.1, U21.19, U22.1, U22.19, U33.13
-SEL3: U23.1, U23.19, U24.1, U24.19, U33.12
-SEL4: U33.11, U40.10, U40.13, U49.1, U49.19, U50.1, U50.19
-SEL5: U33.10, U51.1, U51.19, U52.1, U52.19, U53.2, U53.5
A0: J1.c3, U25.18
A1: J1.c4, U25.16
A2: J1.c5, U25.14
A3: J1.c6, U25.12
A4: J1.c7, U25.9
A5: J1.c8, U25.7
A6: J1.c9, U25.5
A7: J1.c10, U25.3
A8: J1.c11, U26.18
A9: J1.c12, U26.16
A10: J1.c13, U26.14
A11: J1.c14, U26.12
A12: J1.c15, U26.9
A13: J1.c16, U26.7
A14: J1.c17, U26.5
A15: J1.c18, U26.3
CLK: J1.a24, U1.2, U2.2, U3.2, U4.2, U5.2, U6.2, U7.2, U8.2, U9.2, U10.2, U11.2, U12.2, U13.2, U14.2, U15.2, U16.2, U41.2, U42.2, U43.2, U44.2, U45.2, U46.2, U47.2, U48.2
CNTN: U34.1, U39.4
D0: J1.a3, U1.3, U3.3, U5.3, U7.3, U9.3, U11.3, U13.3, U15.3, U29.18, U36.18, U41.3, U43.3, U45.3, U47.3
D1: J1.a4, U1.4, U3.4, U5.4, U7.4, U9.4, U11.4, U13.4, U15.4, U29.16, U36.16, U41.4, U43.4, U45.4, U47.4
D2: J1.a5, U1.5, U3.5, U5.5, U7.5, U9.5, U11.5, U13.5, U15.5, U29.14, U36.14, U41.5, U43.5, U45.5, U47.5
D3: J1.a6, U1.6, U3.6, U5.6, U7.6, U9.6, U11.6, U13.6, U15.6, U29.12, U36.12, U41.6, U43.6, U45.6, U47.6
D4: J1.a7, U2.3, U4.3, U6.3, U8.3, U10.3, U12.3, U14.3, U16.3, U29.9, U36.9, U42.3, U44.3, U46.3, U48.3
D5: J1.a8, U2.4, U4.4, U6.4, U8.4, U10.4, U12.4, U14.4, U16.4, U29.7, U36.7, U42.4, U44.4, U46.4, U48.4
D6: J1.a9, U2.5, U4.5, U6.5, U8.5, U10.5, U12.5, U14.5, U16.5, U29.5, U36.5, U42.5, U44.5, U46.5, U48.5
D7: J1.a10, U2.6, U4.6, U6.6, U8.6, U10.6, U12.6, U14.6, U16.6, U29.3, U36.3, U42.6, U44.6, U46.6, U48.6
DLD0: J1.a16, U30.1
DLD1: J1.a17, U30.2
DLD2: J1.a18, U30.3
DLD3: J1.a19, U30.6
DOE0: J1.a12, U31.1
DOE1: J1.a13, U31.2
DOE2: J1.a14, U31.3
DOE3: J1.a15, U31.6
GND: C1.2, C2.2, C3.2, C4.2, C5.2, C6.2, C7.2, C8.2, C9.2, C10.2, C11.2, C12.2, C13.2, C14.2, C15.2, C16.2, C17.2, C18.2, C19.2, C20.2, C21.2, C22.2, C23.2, C24.2, C25.2, C26.2, C27.2, C28.2, C29.2, C30.2, C31.2, C32.2, C33.2, C34.2, C35.2, C36.2, C37.2, C38.2, C39.2, C40.2, C41.2, C42.2, C43.2, C44.2, C45.2, C46.2, C47.2, C48.2, C49.2, C50.2, C51.2, C52.2, C53.2, J1.a31, J1.a32, J1.b3, J1.b5, J1.b7, J1.b9, J1.b11, J1.b13, J1.b15, J1.b17, J1.b19, J1.b21, J1.b23, J1.b25, J1.b31, J1.b32, J1.c31, J1.c32, LED3.1, U1.8, U1.10, U2.8, U3.8, U4.8, U5.8, U5.10, U6.8, U7.8, U8.8, U9.8, U9.10, U10.8, U11.8, U12.8, U13.8, U13.10, U14.8, U15.8, U16.8, U17.10, U18.10, U19.10, U20.10, U21.10, U22.10, U23.10, U24.10, U25.1, U25.10, U25.19, U26.1, U26.10, U26.19, U27.8, U27.15, U28.8, U28.15, U29.10, U30.4, U30.5, U30.8, U31.4, U31.5, U31.8, U32.8, U33.4, U33.5, U33.8, U34.5, U34.6, U34.7, U34.8, U34.9, U34.11, U34.12, U35.5, U35.7, U35.9, U35.11, U35.13, U36.2, U36.4, U36.6, U36.8, U36.10, U36.11, U36.13, U36.15, U36.17, U37.7, U38.7, U38.9, U38.10, U38.12, U38.13, U39.5, U39.8, U40.7, U41.8, U41.10, U42.8, U43.8, U44.8, U45.8, U45.10, U46.8, U47.8, U48.8, U49.10, U50.10, U51.10, U52.10, U53.7, U53.9, U53.10, U53.12, U53.13
LDK: LED5.1, U38.6
LEDLD: LED5.2, R5.2
LEDP: LED3.2, RP1.2
LEDRD: LED4.2, R4.2
PB0: U17.18, U19.18, U21.18, U23.18, U25.2, U27.2, U49.18, U51.18
PB1: U17.16, U19.16, U21.16, U23.16, U25.4, U27.5, U49.16, U51.16
PB2: U17.14, U19.14, U21.14, U23.14, U25.6, U27.11, U49.14, U51.14
PB3: U17.12, U19.12, U21.12, U23.12, U25.8, U27.14, U49.12, U51.12
PB4: U17.9, U19.9, U21.9, U23.9, U25.11, U28.2, U49.9, U51.9
PB5: U17.7, U19.7, U21.7, U23.7, U25.13, U28.5, U49.7, U51.7
PB6: U17.5, U19.5, U21.5, U23.5, U25.15, U28.11, U49.5, U51.5
PB7: U17.3, U19.3, U21.3, U23.3, U25.17, U28.14, U49.3, U51.3
PB8: U18.18, U20.18, U22.18, U24.18, U26.2, U27.3, U50.18, U52.18
PB9: U18.16, U20.16, U22.16, U24.16, U26.4, U27.6, U50.16, U52.16
PB10: U18.14, U20.14, U22.14, U24.14, U26.6, U27.10, U50.14, U52.14
PB11: U18.12, U20.12, U22.12, U24.12, U26.8, U27.13, U50.12, U52.12
PB12: U18.9, U20.9, U22.9, U24.9, U26.11, U28.3, U50.9, U52.9
PB13: U18.7, U20.7, U22.7, U24.7, U26.13, U28.6, U50.7, U52.7
PB14: U18.5, U20.5, U22.5, U24.5, U26.15, U28.10, U50.5, U52.5
PB15: U18.3, U20.3, U22.3, U24.3, U26.17, U28.13, U50.3, U52.3
PDEC: J1.a23, U34.3, U35.1
PINC: J1.a22, U34.2
POEHP: U27.1, U28.1, U35.4
PQ0_0: U1.14, U17.2
PQ0_1: U1.13, U17.4
PQ0_2: U1.12, U17.6
PQ0_3: U1.11, U17.8
PQ0_4: U2.14, U17.11
PQ0_5: U2.13, U17.13
PQ0_6: U2.12, U17.15
PQ0_7: U2.11, U17.17
PQ0_8: U3.14, U18.2
PQ0_9: U3.13, U18.4
PQ0_10: U3.12, U18.6
PQ0_11: U3.11, U18.8
PQ0_12: U4.14, U18.11
PQ0_13: U4.13, U18.13
PQ0_14: U4.12, U18.15
PQ0_15: U4.11, U18.17
PQ1_0: U5.14, U19.2
PQ1_1: U5.13, U19.4
PQ1_2: U5.12, U19.6
PQ1_3: U5.11, U19.8
PQ1_4: U6.14, U19.11
PQ1_5: U6.13, U19.13
PQ1_6: U6.12, U19.15
PQ1_7: U6.11, U19.17
PQ1_8: U7.14, U20.2
PQ1_9: U7.13, U20.4
PQ1_10: U7.12, U20.6
PQ1_11: U7.11, U20.8
PQ1_12: U8.14, U20.11
PQ1_13: U8.13, U20.13
PQ1_14: U8.12, U20.15
PQ1_15: U8.11, U20.17
PQ2_0: U9.14, U21.2
PQ2_1: U9.13, U21.4
PQ2_2: U9.12, U21.6
PQ2_3: U9.11, U21.8
PQ2_4: U10.14, U21.11
PQ2_5: U10.13, U21.13
PQ2_6: U10.12, U21.15
PQ2_7: U10.11, U21.17
PQ2_8: U11.14, U22.2
PQ2_9: U11.13, U22.4
PQ2_10: U11.12, U22.6
PQ2_11: U11.11, U22.8
PQ2_12: U12.14, U22.11
PQ2_13: U12.13, U22.13
PQ2_14: U12.12, U22.15
PQ2_15: U12.11, U22.17
PQ3_0: U13.14, U23.2
PQ3_1: U13.13, U23.4
PQ3_2: U13.12, U23.6
PQ3_3: U13.11, U23.8
PQ3_4: U14.14, U23.11
PQ3_5: U14.13, U23.13
PQ3_6: U14.12, U23.15
PQ3_7: U14.11, U23.17
PQ3_8: U15.14, U24.2
PQ3_9: U15.13, U24.4
PQ3_10: U15.12, U24.6
PQ3_11: U15.11, U24.8
PQ3_12: U16.14, U24.11
PQ3_13: U16.13, U24.13
PQ3_14: U16.12, U24.15
PQ3_15: U16.11, U24.17
PQ4_0: U41.14, U49.2
PQ4_1: U41.13, U49.4
PQ4_2: U41.12, U49.6
PQ4_3: U41.11, U49.8
PQ4_4: U42.14, U49.11
PQ4_5: U42.13, U49.13
PQ4_6: U42.12, U49.15
PQ4_7: U42.11, U49.17
PQ4_8: U43.14, U50.2
PQ4_9: U43.13, U50.4
PQ4_10: U43.12, U50.6
PQ4_11: U43.11, U50.8
PQ4_12: U44.14, U50.11
PQ4_13: U44.13, U50.13
PQ4_14: U44.12, U50.15
PQ4_15: U44.11, U50.17
PQ5_0: U45.14, U51.2
PQ5_1: U45.13, U51.4
PQ5_2: U45.12, U51.6
PQ5_3: U45.11, U51.8
PQ5_4: U46.14, U51.11
PQ5_5: U46.13, U51.13
PQ5_6: U46.12, U51.15
PQ5_7: U46.11, U51.17
PQ5_8: U47.14, U52.2
PQ5_9: U47.13, U52.4
PQ5_10: U47.12, U52.6
PQ5_11: U47.11, U52.8
PQ5_12: U48.14, U52.11
PQ5_13: U48.13, U52.13
PQ5_14: U48.12, U52.15
PQ5_15: U48.11, U52.17
PSEL0: J1.a20, U32.2, U32.14, U33.1, U39.1
PSEL1: J1.a21, U32.3, U32.13, U33.2, U39.2
PSEL2: J1.c27, U33.3, U39.3, U40.2, U40.5
RB0: U27.4, U29.2
RB1: U27.7, U29.4
RB2: U27.9, U29.6
RB3: U27.12, U29.8
RB4: U28.4, U29.11
RB5: U28.7, U29.13
RB6: U28.9, U29.15
RB7: U28.12, U29.17
RC0_0: U1.15, U2.10
RC0_1: U2.15, U3.10
RC0_2: U3.15, U4.10
RC1_0: U5.15, U6.10
RC1_1: U6.15, U7.10
RC1_2: U7.15, U8.10
RC2_0: U9.15, U10.10
RC2_1: U10.15, U11.10
RC2_2: U11.15, U12.10
RC3_0: U13.15, U14.10
RC3_1: U14.15, U15.10
RC3_2: U15.15, U16.10
RC4_0: U41.15, U42.10
RC4_1: U42.15, U43.10
RC4_2: U43.15, U44.10
RC5_0: U45.15, U46.10
RC5_1: U46.15, U47.10
RC5_2: U47.15, U48.10
RDK: LED4.1, U38.3
UDB: U1.1, U2.1, U3.1, U4.1, U5.1, U6.1, U7.1, U8.1, U9.1, U10.1, U11.1, U12.1, U13.1, U14.1, U15.1, U16.1, U35.2, U41.1, U42.1, U43.1, U44.1, U45.1, U46.1, U47.1, U48.1
VCC: C1.1, C2.1, C3.1, C4.1, C5.1, C6.1, C7.1, C8.1, C9.1, C10.1, C11.1, C12.1, C13.1, C14.1, C15.1, C16.1, C17.1, C18.1, C19.1, C20.1, C21.1, C22.1, C23.1, C24.1, C25.1, C26.1, C27.1, C28.1, C29.1, C30.1, C31.1, C32.1, C33.1, C34.1, C35.1, C36.1, C37.1, C38.1, C39.1, C40.1, C41.1, C42.1, C43.1, C44.1, C45.1, C46.1, C47.1, C48.1, C49.1, C50.1, C51.1, C52.1, C53.1, J1.a1, J1.a2, J1.b1, J1.b2, J1.c1, J1.c2, R4.1, R5.1, RP1.1, U1.16, U2.16, U3.16, U4.16, U5.16, U6.16, U7.16, U8.16, U9.16, U10.16, U11.16, U12.16, U13.16, U14.16, U15.16, U16.16, U17.20, U18.20, U19.20, U20.20, U21.20, U22.20, U23.20, U24.20, U25.20, U26.20, U27.16, U28.16, U29.20, U30.16, U31.16, U32.16, U33.6, U33.16, U34.14, U35.14, U36.20, U37.14, U38.14, U39.6, U39.16, U40.14, U41.16, U42.16, U43.16, U44.16, U45.16, U46.16, U47.16, U48.16, U49.20, U50.20, U51.20, U52.20, U53.14
